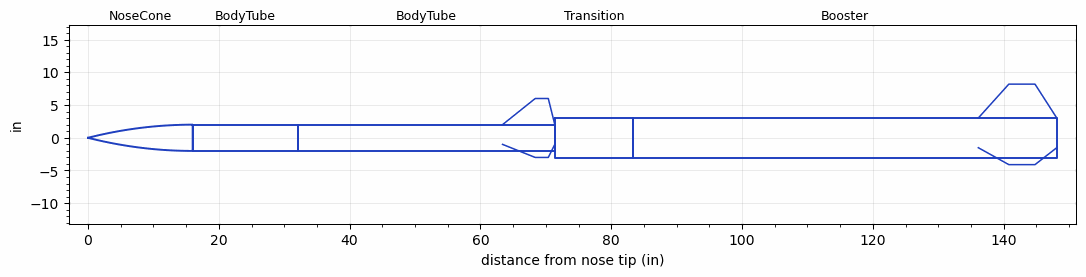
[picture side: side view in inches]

<RASAeroDocument>
 <FileVersion>2</FileVersion>
 <RocketDesign>
  <NoseCone>
   <Length>16</Length>
   <Diameter>4.014</Diameter>
   <Shape>Tangent Ogive</Shape>
   <BluntRadius>0.14</BluntRadius>
   <Location>0</Location>
  </NoseCone>
  <BodyTube>
   <Length>16.125</Length>
   <Diameter>4.014</Diameter>
   <Location>16</Location>
  </BodyTube>
  <BodyTube>
   <Length>39.25</Length>
   <Diameter>4.014</Diameter>
   <Location>32.125</Location>
   <Fin>
    <Count>3</Count>
    <Chord>8</Chord>
    <Span>4</Span>
    <SweepDistance>5</SweepDistance>
    <TipChord>2</TipChord>
    <Thickness>0.125</Thickness>
    <Location>8</Location>
    <AirfoilSection>Square</AirfoilSection>
   </Fin>
  </BodyTube>
  <Transition>
   <Length>12</Length>
   <Diameter>6.05</Diameter>
   <Location>71.375</Location>
   <RearDiameter>6.05</RearDiameter>
  </Transition>
  <Booster>
   <Length>64.75</Length>
   <Diameter>6.05</Diameter>
   <InsideDiameter>6.05</InsideDiameter>
   <Location>83.375</Location>
   <ShoulderLength>0</ShoulderLength>
   <Fin>
    <Count>3</Count>
    <Chord>12</Chord>
    <Span>5.181</Span>
    <SweepDistance>4.67</SweepDistance>
    <TipChord>4</TipChord>
    <Thickness>0.125</Thickness>
    <Location>12</Location>
    <AirfoilSection>Square</AirfoilSection>
   </Fin>
  </Booster>
  <Surface>Smooth (Zero Roughness)</Surface>
  <ModifiedBarrowman>False</ModifiedBarrowman>
  <Turbulence>False</Turbulence>
  <UseBooster1>False</UseBooster1>
  <UseBooster2>False</UseBooster2>
 </RocketDesign>
 <LaunchSite>
  <Altitude>2000</Altitude>
  <Pressure>29.8</Pressure>
  <RodAngle>0</RodAngle>
  <RodLength>60</RodLength>
  <Temperature>81</Temperature>
  <WindSpeed>0</WindSpeed>
 </LaunchSite>
 <Recovery>
  <Altitude1>1000</Altitude1>
  <Altitude2>1000</Altitude2>
  <DeviceType1>None</DeviceType1>
  <DeviceType2>None</DeviceType2>
  <Event1>False</Event1>
  <Event2>False</Event2>
  <Size1>1</Size1>
  <Size2>1</Size2>
  <EventType1>None</EventType1>
  <EventType2>None</EventType2>
  <CD1>1.33</CD1>
  <CD2>1.33</CD2>
 </Recovery>
 <SimulationList>
  <Simulation>
   <SustainerEngine>I435T  (AT)</SustainerEngine>
   <SustainerLaunchWt>9.04</SustainerLaunchWt>
   <SustainerNozzleDiameter>0.5</SustainerNozzleDiameter>
   <SustainerCG>47.5</SustainerCG>
   <SustainerIgnitionDelay>1</SustainerIgnitionDelay>
   <Booster1Engine>L1115  (CTI)</Booster1Engine>
   <Booster1LaunchWt>66</Booster1LaunchWt>
   <Booster1SeparationDelay>0</Booster1SeparationDelay>
   <Booster1IgnitionDelay>0</Booster1IgnitionDelay>
   <Booster1CG>98.79</Booster1CG>
   <Booster1NozzleDiameter>0.5</Booster1NozzleDiameter>
   <IncludeBooster1>True</IncludeBooster1>
   <Booster2Delay>0</Booster2Delay>
   <IncludeBooster2>False</IncludeBooster2>
   <TimetoApogee>20.12027</TimetoApogee>
   <MaxAltitude>5802.86</MaxAltitude>
   <MaxVelocity>716.1027</MaxVelocity>
  </Simulation>
  <Simulation>
   <SustainerLaunchWt>9.04</SustainerLaunchWt>
   <SustainerCG>47.5</SustainerCG>
   <SustainerIgnitionDelay>0</SustainerIgnitionDelay>
   <Booster1Engine>L1115  (CTI)</Booster1Engine>
   <Booster1LaunchWt>30</Booster1LaunchWt>
   <Booster1SeparationDelay>0</Booster1SeparationDelay>
   <Booster1IgnitionDelay>0</Booster1IgnitionDelay>
   <Booster1CG>70</Booster1CG>
   <IncludeBooster1>True</IncludeBooster1>
   <Booster2Delay>0</Booster2Delay>
   <IncludeBooster2>False</IncludeBooster2>
  </Simulation>
 </SimulationList>
</RASAeroDocument>
